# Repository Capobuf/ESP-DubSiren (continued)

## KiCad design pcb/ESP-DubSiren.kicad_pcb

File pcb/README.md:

# ESP-DubSiren PCB V1

Questa cartella contiene la revisione V1 della mainboard per Hammond 29830PSLA. Lo schema è completo e verificato; il layout è una **revisione pre-produzione non autorizzata alla fabbricazione**.

## Stato verificato

- KiCad 10.0.6, schema e PCB a 2 layer.
- Schema: 72 simboli, 69 net nominate, ERC finale 0 errori / 0 warning.
- BOM: 67 componenti logici; audit BOM 0 issues.
- PCB: 100.00 × 74.00 mm, angoli R6.00 mm, 4 fori M3.
- Pre-flight JLCPCB: **NOT READY**.
- DRC: 212 errori, 291 warning/parity, 175 collegamenti non instradati, 503 segnalazioni complessive.
- Non sono stati generati Gerber né package di fabbricazione.

Il routing automatico non è stato accettabile. Il profilo con archi non è esportabile dal backend Specctra disponibile e l’API Konnect installata non espone la cancellazione dei via. Le piste del tentativo sono state rimosse, ma restano 106 via orfani. La scheda non deve essere ordinata.

## Architettura

- U1: ESP32-S3-WROOM-1-N16R8 diretto, non DevKit.
- J1: USB-C USB 2.0 device con Rd 5.1 kΩ, USBLC6-2SC6 e 22 Ω serie.
- U3: LD1117S33TR, +5 V → +3V3.
- U4: MCP3208, SPI, sei canali analogici usati e CH6/CH7 su test point.
- U5: MCP23017, I²C, pulsanti/encoder/mute e GPIO d’espansione.
- U6: Adafruit 6421 PCM5122, I²S + I²C, alimentato a +5 V.
- J2: RCA stereo Switchcraft PJRAS2X1S02X.
- J3: display 2×6; J4: espansione 2×10.
- Top: 5 potenziometri, encoder con push, 4 PB300STQ.
- Rear: MASTER, USB-C e RCA L/R.

Il part number MASTER richiesto inizialmente, PTV111-1415A-B103, non è coerente con il montaggio orizzontale sul rear panel. La V1 usa PTV111-3415A-B103; footprint, pannello e acquisto devono essere confermati sul campione.

## Orientamento meccanico

Il corpo profondo Hammond è la parte superiore. I controlli sono sul lato B e attraversano il top; l’elettronica è sul lato F verso il coperchio inferiore.

La PCB centrata lascia 1.415 mm per lato in X e 1.565 mm in Y rispetto al lid 102.83 × 77.13 mm; rispetto al vano corpo 104.71 × 79.41 mm lascia 2.355 e 2.705 mm. H2 è arretrato a (95,31) per evitare antenna/courtyard WROOM.

Stima Z non validata: parete-top → PCB 10–11 mm; con PCB 1.6 mm restano 17–18 mm nominali verso il fondo. Il DAC su header è stimato 8–10 mm sotto PCB, quindi margine teorico 7–10 mm prima di tolleranze, saldature e cavi.

## DRC finale

| Quantità | Regola |
|---:|---|
| 106 | via_dangling |
| 39 | silk_over_copper |
| 26 | lib_footprint_mismatch |
| 20 | silk_overlap |
| 13 | nonmirrored_text_on_back_layer |
| 12 | hole_to_hole |
| 12 | drill_out_of_range |
| 10 | pth_inside_courtyard |
| 5 | courtyards_overlap |
| 3 | clearance |
| 3 | hole_clearance |
| 3 | starved_thermal |
| 3 | silk_edge_clearance |
| 1 | npth_inside_courtyard |

Alle 256 violazioni sopra si aggiungono 175 unconnected e 72 segnalazioni di parità schema/footprint. I 12 fori da 0.20 mm sono i thermal-via del footprint ufficiale WROOM. Gli overlap maggiori coinvolgono WROOM/antenna, U6/RV5, U5/SW4 e l’area J2.

## File

- [BOM-V1.md](BOM-V1.md) e [reports/bom-v1.csv](reports/bom-v1.csv)
- [PINOUT-V1.md](PINOUT-V1.md)
- [MECHANICAL-V1.md](MECHANICAL-V1.md)
- [SOURCES-V1.md](SOURCES-V1.md)
- [erc-v1.json](erc-v1.json) e [drc-v1.json](drc-v1.json)
- disegni 1:1 in [mechanical](mechanical), immagini in [screenshots](screenshots), export in [outputs](outputs)

## Prima della prossima revisione

1. Rimuovere i 106 via orfani con un backend Konnect che supporti la cancellazione via o ricostruire il PCB.
2. Rivedere placement e dimensione scheda, poi instradare integralmente.
3. Portare DRC e unconnected a zero.
4. Misurare componenti meccanici, aggiornare footprint/pannelli e provare lo stack nel box.
5. Solo dopo generare Gerber, drill e package fab.

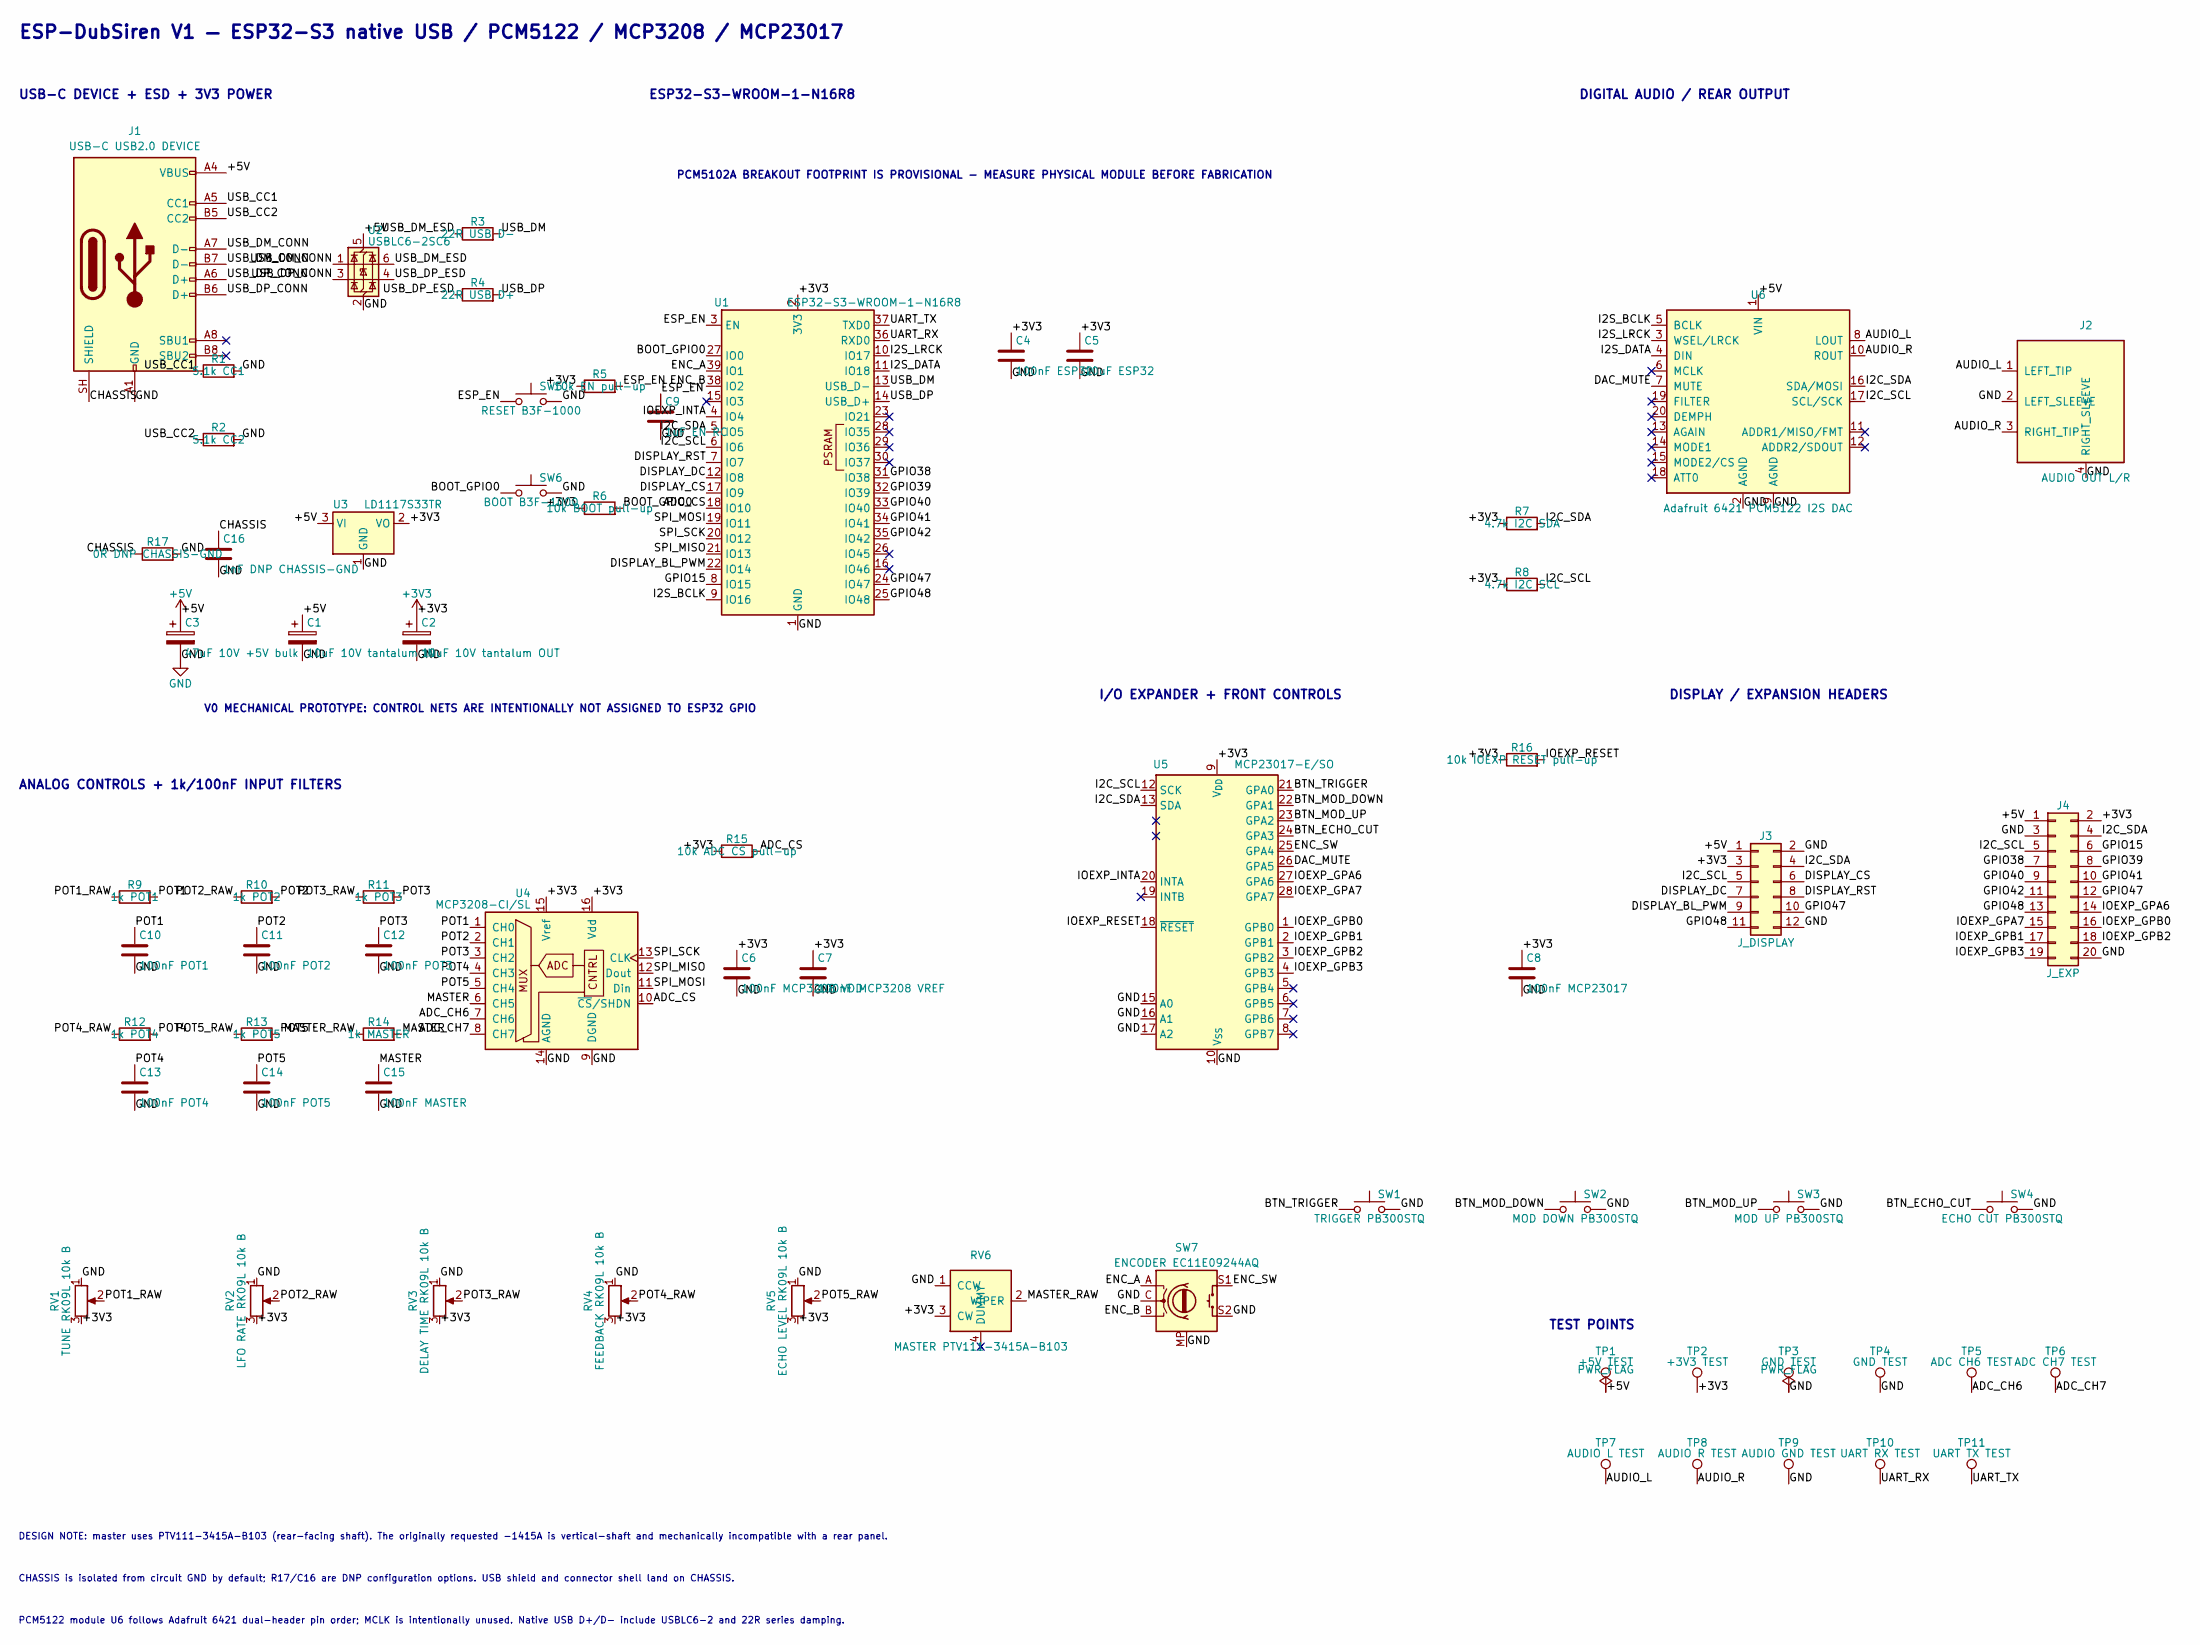
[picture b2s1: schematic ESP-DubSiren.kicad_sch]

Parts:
C1: 10uF 10V tantalum IN; CP_EIA-3528-21_Kemet-B
C2: 10uF 10V tantalum OUT; CP_EIA-3528-21_Kemet-B
C3: 47uF 10V +5V bulk; CP_Elec_6.3x5.3
C4: 100nF ESP32; C_0603_1608Metric
C5: 10uF ESP32; C_1206_3216Metric
C6: 100nF MCP3208 VDD; C_0603_1608Metric
C7: 100nF MCP3208 VREF; C_0603_1608Metric
C8: 100nF MCP23017; C_0603_1608Metric
C9: 1uF EN RC; C_0805_2012Metric
C10: 100nF POT1; C_0603_1608Metric
C11: 100nF POT2; C_0603_1608Metric
C12: 100nF POT3; C_0603_1608Metric
C13: 100nF POT4; C_0603_1608Metric
C14: 100nF POT5; C_0603_1608Metric
C15: 100nF MASTER; C_0603_1608Metric
C16: 1nF DNP CHASSIS-GND; C_0603_1608Metric
J1: USB-C USB2.0 DEVICE; USB_C_Receptacle_GCT_USB4085; MPN USB4085-GF-A
J2: AUDIO OUT L/R; Switchcraft_PJRAS2X1S02X; MPN PJRAS2X1S02X
J3: J_DISPLAY; PinHeader_2x06_P2.54mm_Vertical
J4: J_EXP; PinHeader_2x10_P2.54mm_Vertical
R1: 5.1k CC1; R_0603_1608Metric
R2: 5.1k CC2; R_0603_1608Metric
R3: 22R USB D-; R_0603_1608Metric
R4: 22R USB D+; R_0603_1608Metric
R5: 10k EN pull-up; R_0603_1608Metric
R6: 10k BOOT pull-up; R_0603_1608Metric
R7: 4.7k I2C SDA; R_0603_1608Metric
R8: 4.7k I2C SCL; R_0603_1608Metric
R9: 1k POT1; R_0603_1608Metric
R10: 1k POT2; R_0603_1608Metric
R11: 1k POT3; R_0603_1608Metric
R12: 1k POT4; R_0603_1608Metric
R13: 1k POT5; R_0603_1608Metric
R14: 1k MASTER; R_0603_1608Metric
R15: 10k ADC CS pull-up; R_0603_1608Metric
R16: 10k IOEXP RESET pull-up; R_0603_1608Metric
R17: 0R DNP CHASSIS-GND; R_0603_1608Metric
RV1: TUNE RK09L 10k B; Potentiometer_Alps_RK09L_Single_Vertical
RV2: LFO RATE RK09L 10k B; Potentiometer_Alps_RK09L_Single_Vertical
RV3: DELAY TIME RK09L 10k B; Potentiometer_Alps_RK09L_Single_Vertical
RV4: FEEDBACK RK09L 10k B; Potentiometer_Alps_RK09L_Single_Vertical
RV5: ECHO LEVEL RK09L 10k B; Potentiometer_Alps_RK09L_Single_Vertical
RV6: MASTER PTV111-3415A-B103; Bourns_PTV111-3415A-B103; MPN PTV111-3415A-B103
SW1: TRIGGER PB300STQ; PB300STQ; MPN PB300STQ
SW2: MOD DOWN PB300STQ; PB300STQ; MPN PB300STQ
SW3: MOD UP PB300STQ; PB300STQ; MPN PB300STQ
SW4: ECHO CUT PB300STQ; PB300STQ; MPN PB300STQ
SW5: RESET B3F-1000; SW_PUSH_6mm_H4.3mm
SW6: BOOT B3F-1000; SW_PUSH_6mm_H4.3mm
SW7: ENCODER EC11E09244AQ; RotaryEncoder_Alps_EC11E-Switch_Vertical_H20mm
TP1: +5V TEST; TestPoint_Pad_D1.0mm
TP2: +3V3 TEST; TestPoint_Pad_D1.0mm
TP3, TP4: GND TEST; TestPoint_Pad_D1.0mm
TP5: ADC CH6 TEST; TestPoint_Pad_D1.0mm
TP6: ADC CH7 TEST; TestPoint_Pad_D1.0mm
TP7: AUDIO L TEST; TestPoint_Pad_D1.0mm
TP8: AUDIO R TEST; TestPoint_Pad_D1.0mm
TP9: AUDIO GND TEST; TestPoint_Pad_D1.0mm
TP10: UART RX TEST; TestPoint_Pad_D1.0mm
TP11: UART TX TEST; TestPoint_Pad_D1.0mm
U1: ESP32-S3-WROOM-1-N16R8; ESP32-S3-WROOM-1; MPN ESP32-S3-WROOM-1-N16R8
U2: USBLC6-2SC6; SOT-23-6; MPN USBLC6-2SC6
U3: LD1117S33TR; SOT-223-3_TabPin2; MPN LD1117S33TR
U4: MCP3208-CI/SL; SOIC-16_3.9x9.9mm_P1.27mm; MPN MCP3208-CI/SL
U5: MCP23017-E/SO; SOIC-28W_7.5x17.9mm_P1.27mm; MPN MCP23017-E/SO
U6: Adafruit 6421 PCM5122 I2S DAC; Adafruit_PCM5122_6421; MPN 6421

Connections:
+3V3: C2.1, C4.1, C5.1, C6.1, C7.1, C8.1, J3.3, J4.2, R5.1, R6.1, R7.1, R8.1, R15.1, R16.1, RV1.3, RV2.3, RV3.3, RV4.3, RV5.3, RV6.3 (CW), TP2.1, U1.2 (3V3), U3.2 (VO), U4.15 (Vref), U4.16 (Vdd), U5.9 (V_{DD})
/ADC_CH6: TP5.1, U4.7 (CH6)
/ADC_CH7: TP6.1, U4.8 (CH7)
/ADC_CS: R15.2, U1.18 (IO10), U4.10 (~CS/SHDN)
/AUDIO_L: J2.1 (LEFT_TIP), TP7.1, U6.8 (LOUT)
/AUDIO_R: J2.3 (RIGHT_TIP), TP8.1, U6.10 (ROUT)
/BOOT_GPIO0: R6.2, SW6.1, U1.27 (IO0)
/BTN_ECHO_CUT: SW4.1, U5.24 (GPA3)
/BTN_MOD_DOWN: SW2.1, U5.22 (GPA1)
/BTN_MOD_UP: SW3.1, U5.23 (GPA2)
/BTN_TRIGGER: SW1.1, U5.21 (GPA0)
/CHASSIS: C16.1, J1.SH (SHIELD), R17.1
/DAC_MUTE: U5.26 (GPA5), U6.7 (MUTE)
/DISPLAY_BL_PWM: J3.9, U1.22 (IO14)
/DISPLAY_CS: J3.6, U1.17 (IO9)
/DISPLAY_DC: J3.7, U1.12 (IO8)
/DISPLAY_RST: J3.8, U1.7 (IO7)
/ENC_A: SW7.A, U1.39 (IO1)
/ENC_B: SW7.B, U1.38 (IO2)
/ENC_SW: SW7.S1, U5.25 (GPA4)
/ESP_EN: C9.1, R5.2, SW5.1, U1.3 (EN)
/GPIO15: J4.6, U1.8 (IO15)
/GPIO38: J4.7, U1.31 (IO38)
/GPIO39: J4.8, U1.32 (IO39)
/GPIO40: J4.9, U1.33 (IO40)
/GPIO41: J4.10, U1.34 (IO41)
/GPIO42: J4.11, U1.35 (IO42)
/GPIO47: J3.10, J4.12, U1.24 (IO47)
/GPIO48: J3.11, J4.13, U1.25 (IO48)
/I2C_SCL: J3.5, J4.5, R8.2, U1.6 (IO6), U5.12 (SCK), U6.17 (SCL/SCK)
/I2C_SDA: J3.4, J4.4, R7.2, U1.5 (IO5), U5.13 (SDA), U6.16 (SDA/MOSI)
/I2S_BCLK: U1.9 (IO16), U6.5 (BCLK)
/I2S_DATA: U1.11 (IO18), U6.4 (DIN)
/I2S_LRCK: U1.10 (IO17), U6.3 (WSEL/LRCK)
/IOEXP_GPA6: J4.14, U5.27 (GPA6)
/IOEXP_GPA7: J4.15, U5.28 (GPA7)
/IOEXP_GPB0: J4.16, U5.1 (GPB0)
/IOEXP_GPB1: J4.17, U5.2 (GPB1)
/IOEXP_GPB2: J4.18, U5.3 (GPB2)
/IOEXP_GPB3: J4.19, U5.4 (GPB3)
/IOEXP_INTA: U1.4 (IO4), U5.20 (INTA)
/IOEXP_RESET: R16.2, U5.18 (~RESET)
/MASTER: C15.1, R14.2, U4.6 (CH5)
/MASTER_RAW: R14.1, RV6.2 (WIPER)
/POT1: C10.1, R9.2, U4.1 (CH0)
/POT1_RAW: R9.1, RV1.2
/POT2: C11.1, R10.2, U4.2 (CH1)
/POT2_RAW: R10.1, RV2.2
/POT3: C12.1, R11.2, U4.3 (CH2)
/POT3_RAW: R11.1, RV3.2
/POT4: C13.1, R12.2, U4.4 (CH3)
/POT4_RAW: R12.1, RV4.2
/POT5: C14.1, R13.2, U4.5 (CH4)
/POT5_RAW: R13.1, RV5.2
/SPI_MISO: U1.21 (IO13), U4.12 (Dout)
/SPI_MOSI: U1.19 (IO11), U4.11 (Din)
/SPI_SCK: U1.20 (IO12), U4.13 (CLK)
/UART_RX: TP10.1, U1.36 (RXD0)
/UART_TX: TP11.1, U1.37 (TXD0)
/USB_CC1: J1.A5 (CC1), R1.1
/USB_CC2: J1.B5 (CC2), R2.1
/USB_DM: R3.2, U1.13 (USB_D-)
/USB_DM_CONN: J1.A7 (D-), J1.B7 (D-), U2.1 (I/O1)
/USB_DM_ESD: R3.1, U2.6 (I/O1)
/USB_DP: R4.2, U1.14 (USB_D+)
/USB_DP_CONN: J1.A6 (D+), J1.B6 (D+), U2.3 (I/O2)
/USB_DP_ESD: R4.1, U2.4 (I/O2)

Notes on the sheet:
V0 MECHANICAL PROTOTYPE: CONTROL NETS ARE INTENTIONALLY NOT ASSIGNED TO ESP32 GPIO
PCM5102A BREAKOUT FOOTPRINT IS PROVISIONAL - MEASURE PHYSICAL MODULE BEFORE FABRICATION
ESP-DubSiren V1 — ESP32-S3 native USB / PCM5122 / MCP3208 / MCP23017
USB-C DEVICE + ESD + 3V3 POWER
ESP32-S3-WROOM-1-N16R8
DIGITAL AUDIO / REAR OUTPUT
ANALOG CONTROLS + 1k/100nF INPUT FILTERS
I/O EXPANDER + FRONT CONTROLS
DISPLAY / EXPANSION HEADERS
TEST POINTS
DESIGN NOTE: master uses PTV111-3415A-B103 (rear-facing shaft). The originally requested -1415A is vertical-shaft and mechanically incompatible with a rear panel.
CHASSIS is isolated from circuit GND by default; R17/C16 are DNP configuration options. USB shield and connector shell land on CHASSIS.
PCM5122 module U6 follows Adafruit 6421 dual-header pin order; MCLK is intentionally unused. Native USB D+/D- include USBLC6-2 and 22R series damping.

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
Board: 2 copper layers, 72 parts (12 on the bottom side), 69 nets, no tracks yet.

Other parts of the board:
H1, H2, H3, H4: MountingHole_3.2mm_M3
MECH1: Hammond_29830PSLA_REFERENCE

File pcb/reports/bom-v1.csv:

"Reference","Value","Manufacturer","MPN","Footprint","Datasheet","Quantity"
"C1","10uF 10V tantalum IN","","","Capacitor_Tantalum_SMD:CP_EIA-3528-21_Kemet-B","","1"
"C2","10uF 10V tantalum OUT","","","Capacitor_Tantalum_SMD:CP_EIA-3528-21_Kemet-B","","1"
"C3","47uF 10V +5V bulk","","","Capacitor_SMD:CP_Elec_6.3x5.3","","1"
"C4","100nF ESP32","","","Capacitor_SMD:C_0603_1608Metric","","1"
"C5","10uF ESP32","","","Capacitor_SMD:C_1206_3216Metric","","1"
"C6","100nF MCP3208 VDD","","","Capacitor_SMD:C_0603_1608Metric","","1"
"C7","100nF MCP3208 VREF","","","Capacitor_SMD:C_0603_1608Metric","","1"
"C8","100nF MCP23017","","","Capacitor_SMD:C_0603_1608Metric","","1"
"C9","1uF EN RC","","","Capacitor_SMD:C_0805_2012Metric","","1"
"C10","100nF POT1","","","Capacitor_SMD:C_0603_1608Metric","","1"
"C11","100nF POT2","","","Capacitor_SMD:C_0603_1608Metric","","1"
"C12","100nF POT3","","","Capacitor_SMD:C_0603_1608Metric","","1"
"C13","100nF POT4","","","Capacitor_SMD:C_0603_1608Metric","","1"
"C14","100nF POT5","","","Capacitor_SMD:C_0603_1608Metric","","1"
"C15","100nF MASTER","","","Capacitor_SMD:C_0603_1608Metric","","1"
"C16","1nF DNP CHASSIS-GND","","","Capacitor_SMD:C_0603_1608Metric","","1"
"J1","USB-C USB2.0 DEVICE","GCT","USB4085-GF-A","Connector_USB:USB_C_Receptacle_GCT_USB4085","https://www.usb.org/sites/default/files/documents/usb_type-c.zip","1"
"J2","AUDIO OUT L/R","Switchcraft","PJRAS2X1S02X","ESP-DubSiren:Switchcraft_PJRAS2X1S02X","https://www.switchcraft.com/assets/1/24/pjras2x1s__x_series_cd.pdf","1"
"J3","J_DISPLAY","","","Connector_PinHeader_2.54mm:PinHeader_2x06_P2.54mm_Vertical","","1"
"J4","J_EXP","","","Connector_PinHeader_2.54mm:PinHeader_2x10_P2.54mm_Vertical","","1"
"R1","5.1k CC1","","","Resistor_SMD:R_0603_1608Metric","","1"
"R2","5.1k CC2","","","Resistor_SMD:R_0603_1608Metric","","1"
"R3","22R USB D-","","","Resistor_SMD:R_0603_1608Metric","","1"
"R4","22R USB D+","","","Resistor_SMD:R_0603_1608Metric","","1"
"R5","10k EN pull-up","","","Resistor_SMD:R_0603_1608Metric","","1"
"R6","10k BOOT pull-up","","","Resistor_SMD:R_0603_1608Metric","","1"
"R7","4.7k I2C SDA","","","Resistor_SMD:R_0603_1608Metric","","1"
"R8","4.7k I2C SCL","","","Resistor_SMD:R_0603_1608Metric","","1"
"R9","1k POT1","","","Resistor_SMD:R_0603_1608Metric","","1"
"R10","1k POT2","","","Resistor_SMD:R_0603_1608Metric","","1"
"R11","1k POT3","","","Resistor_SMD:R_0603_1608Metric","","1"
"R12","1k POT4","","","Resistor_SMD:R_0603_1608Metric","","1"
"R13","1k POT5","","","Resistor_SMD:R_0603_1608Metric","","1"
"R14","1k MASTER","","","Resistor_SMD:R_0603_1608Metric","","1"
"R15","10k ADC CS pull-up","","","Resistor_SMD:R_0603_1608Metric","","1"
"R16","10k IOEXP RESET pull-up","","","Resistor_SMD:R_0603_1608Metric","","1"
"R17","0R DNP CHASSIS-GND","","","Resistor_SMD:R_0603_1608Metric","","1"
"RV1","TUNE RK09L 10k B","","","Potentiometer_THT:Potentiometer_Alps_RK09L_Single_Vertical","","1"
"RV2","LFO RATE RK09L 10k B","","","Potentiometer_THT:Potentiometer_Alps_RK09L_Single_Vertical","","1"
"RV3","DELAY TIME RK09L 10k B","","","Potentiometer_THT:Potentiometer_Alps_RK09L_Single_Vertical","","1"
"RV4","FEEDBACK RK09L 10k B","","","Potentiometer_THT:Potentiometer_Alps_RK09L_Single_Vertical","","1"
"RV5","ECHO LEVEL RK09L 10k B","","","Potentiometer_THT:Potentiometer_Alps_RK09L_Single_Vertical","","1"
"RV6","MASTER PTV111-3415A-B103","Bourns","PTV111-3415A-B103","ESP-DubSiren:Bourns_PTV111-3415A-B103","https://www.bourns.com/docs/default-document-library/ptvptt.pdf","1"
"SW1","TRIGGER PB300STQ","E-Switch","PB300STQ","ESP-DubSiren:PB300STQ","","1"
"SW2","MOD DOWN PB300STQ","E-Switch","PB300STQ","ESP-DubSiren:PB300STQ","","1"
"SW3","MOD UP PB300STQ","E-Switch","PB300STQ","ESP-DubSiren:PB300STQ","","1"
"SW4","ECHO CUT PB300STQ","E-Switch","PB300STQ","ESP-DubSiren:PB300STQ","","1"
"SW5","RESET B3F-1000","","","Button_Switch_THT:SW_PUSH_6mm_H4.3mm","","1"
"SW6","BOOT B3F-1000","","","Button_Switch_THT:SW_PUSH_6mm_H4.3mm","","1"
"SW7","ENCODER EC11E09244AQ","","","Rotary_Encoder:RotaryEncoder_Alps_EC11E-Switch_Vertical_H20mm","","1"
"TP1","+5V TEST","","","TestPoint:TestPoint_Pad_D1.0mm","","1"
"TP2","+3V3 TEST","","","TestPoint:TestPoint_Pad_D1.0mm","","1"
"TP3,TP4","GND TEST","","","TestPoint:TestPoint_Pad_D1.0mm","","2"
"TP5","ADC CH6 TEST","","","TestPoint:TestPoint_Pad_D1.0mm","","1"
"TP6","ADC CH7 TEST","","","TestPoint:TestPoint_Pad_D1.0mm","","1"
"TP7","AUDIO L TEST","","","TestPoint:TestPoint_Pad_D1.0mm","","1"
"TP8","AUDIO R TEST","","","TestPoint:TestPoint_Pad_D1.0mm","","1"
"TP9","AUDIO GND TEST","","","TestPoint:TestPoint_Pad_D1.0mm","","1"
"TP10","UART RX TEST","","","TestPoint:TestPoint_Pad_D1.0mm","","1"
"TP11","UART TX TEST","","","TestPoint:TestPoint_Pad_D1.0mm","","1"
"U1","ESP32-S3-WROOM-1-N16R8","Espressif Systems","ESP32-S3-WROOM-1-N16R8","RF_Module:ESP32-S3-WROOM-1","https://www.espressif.com/sites/default/files/documentation/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","1"
"U2","USBLC6-2SC6","STMicroelectronics","USBLC6-2SC6","Package_TO_SOT_SMD:SOT-23-6","https://www.st.com/resource/en/datasheet/usblc6-2.pdf","1"
"U3","LD1117S33TR","STMicroelectronics","LD1117S33TR","Package_TO_SOT_SMD:SOT-223-3_TabPin2","http://www.st.com/st-web-ui/static/active/en/resource/techni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","1"
"U4","MCP3208-CI/SL","Microchip Technology","MCP3208-CI/SL","Package_SO:SOIC-16_3.9x9.9mm_P1.27mm","http://ww1.microchip.com/downloads/en/DeviceDoc/21298c.pdf","1"
"U5","MCP23017-E/SO","Microchip Technology","MCP23017-E/SO","Package_SO:SOIC-28W_7.5x17.9mm_P1.27mm","https://ww1.microchip.com/downloads/aemDocuments/documents/A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","1"
"U6","Adafruit 6421 PCM5122 I2S DAC","Adafruit","6421","ESP-DubSiren:Adafruit_PCM5122_6421","https://github.com/adafruit/Adafruit-PCM5122-I2S-DAC-PCB","1"
